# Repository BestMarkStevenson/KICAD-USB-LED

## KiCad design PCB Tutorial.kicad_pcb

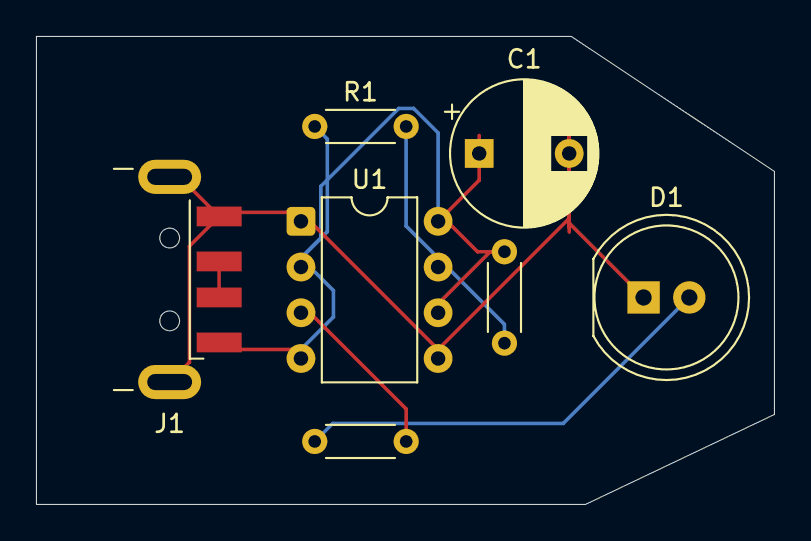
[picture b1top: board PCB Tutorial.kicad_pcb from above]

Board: 2 copper layers, 41.0 x 26.0 mm, 7 parts (0 on the bottom side), 6 nets.

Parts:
C1: C; CP_Radial_D8.0mm_P5.00mm
D1: LED; LED_D8.0mm
J1: USB_A; USB_A_CNCTech_1001-011-01101_Horizontal
R1: R; R_Axial_DIN0204_L3.6mm_D1.6mm_P5.08mm_Horizontal
R2: R2; R_Axial_DIN0204_L3.6mm_D1.6mm_P5.08mm_Horizontal
R3: R3; R_Axial_DIN0204_L3.6mm_D1.6mm_P5.08mm_Horizontal
U1: NE555P; DIP-8_W7.62mm

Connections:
GND: C1.2, D1.1 (K), J1.4 (GND), J1.5 (Shield), U1.1 (GND), U1.5 (CV)
unnamed: D1.2 (A), R3.1
unnamed: J1.2 (D-), J1.3 (D+)
unnamed: R1.2, R2.1, U1.7 (DIS)
unnamed: R3.2, U1.3 (Q)
VCC: C1.1, J1.1 (VBUS), R1.1, R2.2, U1.2 (TR), U1.4 (R), U1.6 (THR), U1.8 (VCC)

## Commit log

2025-08-19 Screenshots of PCB and Schematic
2025-08-19 Added Real Life Picture
2025-08-19 Uploaded video of KICAD USB LED lighting up
